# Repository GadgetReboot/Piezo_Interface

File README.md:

# Piezo_Interface
4 Channel Piezo element signal conditioner for triggering analog/digital inputs

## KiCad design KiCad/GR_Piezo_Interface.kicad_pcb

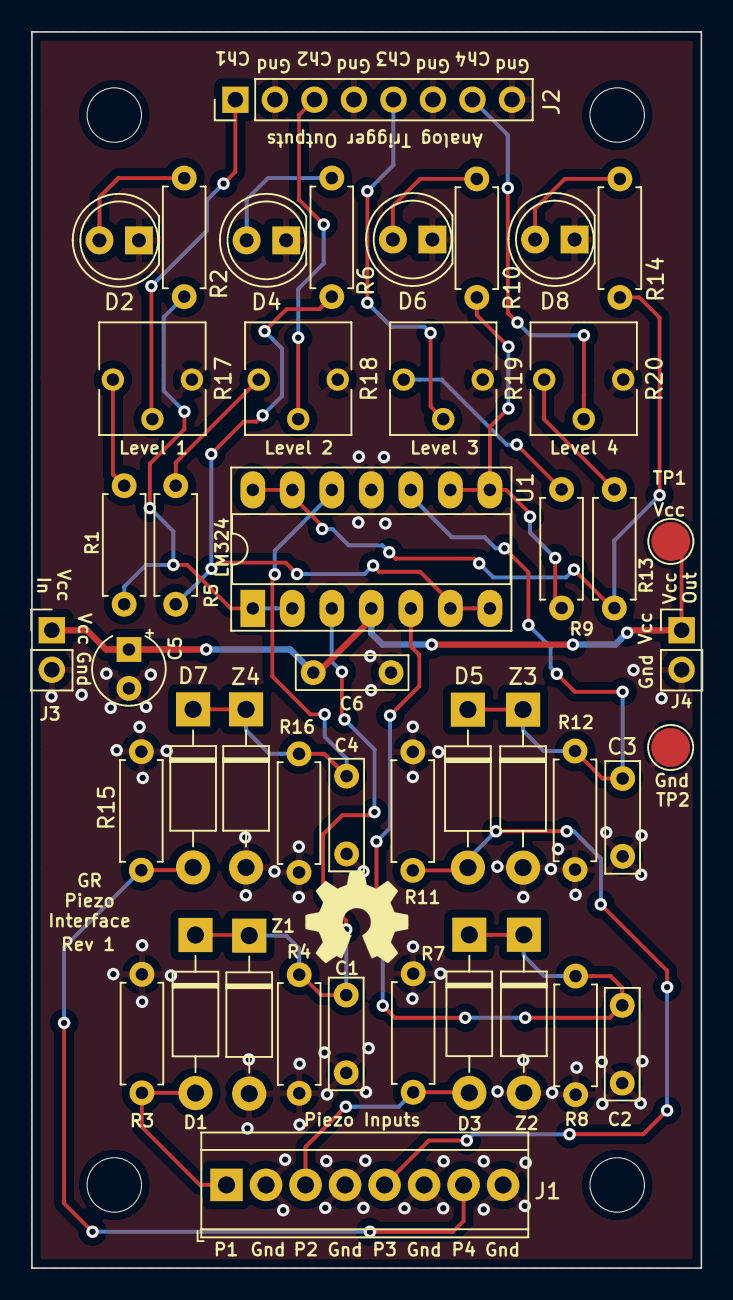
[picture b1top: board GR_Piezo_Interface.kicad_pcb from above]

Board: 2 copper layers, 43.0 x 79.5 mm, 49 parts (0 on the bottom side), 26 nets.

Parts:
C1, C2, C3, C4: 10nF; C_Rect_L7.0mm_W2.0mm_P5.00mm
C5: 10uF; CP_Radial_Tantal_D4.5mm_P2.50mm
C6: 100nF; C_Rect_L7.0mm_W2.0mm_P5.00mm
D1, D3, D5, D7: 1N4148; D_DO-41_SOD81_P10.16mm_Horizontal
D2, D4, D6, D8: LED_Small_ALT; LED_D5.0mm
J1: Screw_Terminal_01x08; TerminalBlock_TE_282834-8_1x08_P2.54mm_Horizontal
J2: Conn_01x08; PinHeader_1x08_P2.54mm_Vertical
J3: Vin; PinHeader_1x02_P2.54mm_Vertical
J4: Vout; PinHeader_1x02_P2.54mm_Vertical
MH1, MH2, MH3, MH4: MountingHole; MountingHole_3.5mm
R1, R5, R9, R13: 100r; R_Axial_DIN0207_L6.3mm_D2.5mm_P7.62mm_Horizontal
R2, R6, R10, R14: 330r; R_Axial_DIN0207_L6.3mm_D2.5mm_P7.62mm_Horizontal
R3, R7, R11, R15: 100K; R_Axial_DIN0207_L6.3mm_D2.5mm_P7.62mm_Horizontal
R4, R8, R12, R16: 1M; R_Axial_DIN0207_L6.3mm_D2.5mm_P7.62mm_Horizontal
R17, R18, R19, R20: 10K; Potentiometer_Vishay_T73YP_Vertical
TP1: VCC Test Point; TestPoint_Pad_D2.5mm
TP2: GND Test Point; TestPoint_Pad_D2.5mm
U1: LM324; DIP-14_W7.62mm_Socket_LongPads
Z1, Z2, Z3, Z4: 5.1V; D_DO-41_SOD81_P10.16mm_Horizontal

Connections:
/Out_1: J2.1, R17.2
/Out_2: J2.3, R18.2
/Out_3: J2.5, R19.2
/Out_4: J2.7, R20.2
/Piezo1: D1.2, J1.1, R3.1
/Piezo2: D3.2, J1.3, R7.1
/Piezo3: D5.2, J1.5, R11.1
/Piezo4: D7.2, J1.7, R15.1
GNDREF: C1.2, C2.2, C3.2, C4.2, C5.2, C6.2, D2.1, D4.1, D6.1, D8.1, J1.2, J1.4, J1.6, J1.8, J2.2, J2.4, J2.6, J2.8, J3.2, J4.2, R3.2, R4.2, R7.2, R8.2, R11.2, R12.2, R15.2, R16.2, R17.3, R18.3, R19.3, R20.3, TP2.1, U1.11, Z1.2, Z2.2, Z3.2, Z4.2
unnamed: C1.1, D1.1, R4.1, U1.3, Z1.1
unnamed: C2.1, D3.1, R8.1, U1.5, Z2.1
unnamed: C3.1, D5.1, R12.1, U1.10, Z3.1
unnamed: C4.1, D7.1, R16.1, U1.12, Z4.1
unnamed: D2.2, R2.2
unnamed: D4.2, R6.2
unnamed: D6.2, R10.2
unnamed: D8.2, R14.2
unnamed: R1.1, R2.1, U1.1, U1.2
unnamed: R1.2, R17.1
unnamed: R5.1, R6.1, U1.6, U1.7
unnamed: R9.1, R10.1, U1.8, U1.9
unnamed: R13.1, R14.1, U1.13, U1.14
unnamed: R13.2, R20.1
unnamed: R5.2, R18.1
unnamed: R9.2, R19.1
VCC: C5.1, C6.1, J3.1, J4.1, TP1.1, U1.4

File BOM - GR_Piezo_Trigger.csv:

Piezo Trigger BOM,,,,,,,,
,,,,,,,,
Item #,Reference Designator,Qty,Manufacturer,Mfg Part #,Description / Value,Package/Footprint ,Type,Instructions / Notes
1,C1 C2 C3 C4,4,Vishay,K103K15X7RF5TH5,10000 pF ±10% 50V Ceramic Capacitor X7R Radial,5mm Pitch,THRU-HOLE,
2,C6,1,Vishay,K104K15X7RF5TH5,0.1 µF ±10% 50V Ceramic Capacitor X7R Radial,5mm Pitch,THRU-HOLE,
3,C5,1,Panasonic,ECA-1CM100I,10 µF 16 V Aluminum Electrolytic Capacitor Radial,2.5mm Pitch,THRU-HOLE,
4,D1 D3 D5 D7,4,Onsemi,1N4148,DIODE GEN PURP 100V 200MA DO35,DO35,THRU-HOLE,
5,D2 D4 D6 D8,4,Kingbright,WP7113ID,LED RED DIFFUSED T-1 3/4 T/H,T-1 3/4,THRU-HOLE,
6,J2,1,Sullins Connector Solutions,PREC008SAAN-RC,"Connector Header Through Hole 8 position 0.100""",8POS,THRU-HOLE,
7,J1,1,Phoenix Contact,1729186,TERM BLK 8P SIDE ENT 5.08MM PCB,8POS,THRU-HOLE,
8,J3 J4,2,Sullins Connector Solutions,PREC002SAAN-RC,"Connector Header Through Hole 2 position 0.100""",2POS,THRU-HOLE,
9,R1 R5 R9 R13,4,YAGEO,CFR-25JR-52-100R,RES 100 OHM 5% 1/4W AXIAL,Axial,THRU-HOLE,
10,R2 R6 R10 R14,4,YAGEO,CFR-25JR-52-330R,RES 330 OHM 5% 1/4W AXIAL,Axial,THRU-HOLE,
11,R17 R18 R19 R20,4,Vishay,T73YP103KT20,TRIMMER 10K OHM 0.5W PC PIN TOP,2.5mm Pitch,THRU-HOLE,
12,R3 R7 R11 R15,4,YAGEO,CFR-25JR-52-100K,RES 100K OHM 5% 1/4W AXIAL,Axial,THRU-HOLE,
13,R4 R8 R12 R16,4,YAGEO,CFR-25JR-52-1M,RES 1M OHM 5% 1/4W AXIAL,Axial,THRU-HOLE,
14,U1,1,Texas Instruments,LM324N,IC OPAMP GP 4 CIRCUIT 14DIP,DIP-14,THRU-HOLE,
15,Z1 Z2 Z3 Z4,4,Onsemi,1N5231B,DIODE ZENER 5.1V 500MW DO35,DO35,THRU-HOLE,
